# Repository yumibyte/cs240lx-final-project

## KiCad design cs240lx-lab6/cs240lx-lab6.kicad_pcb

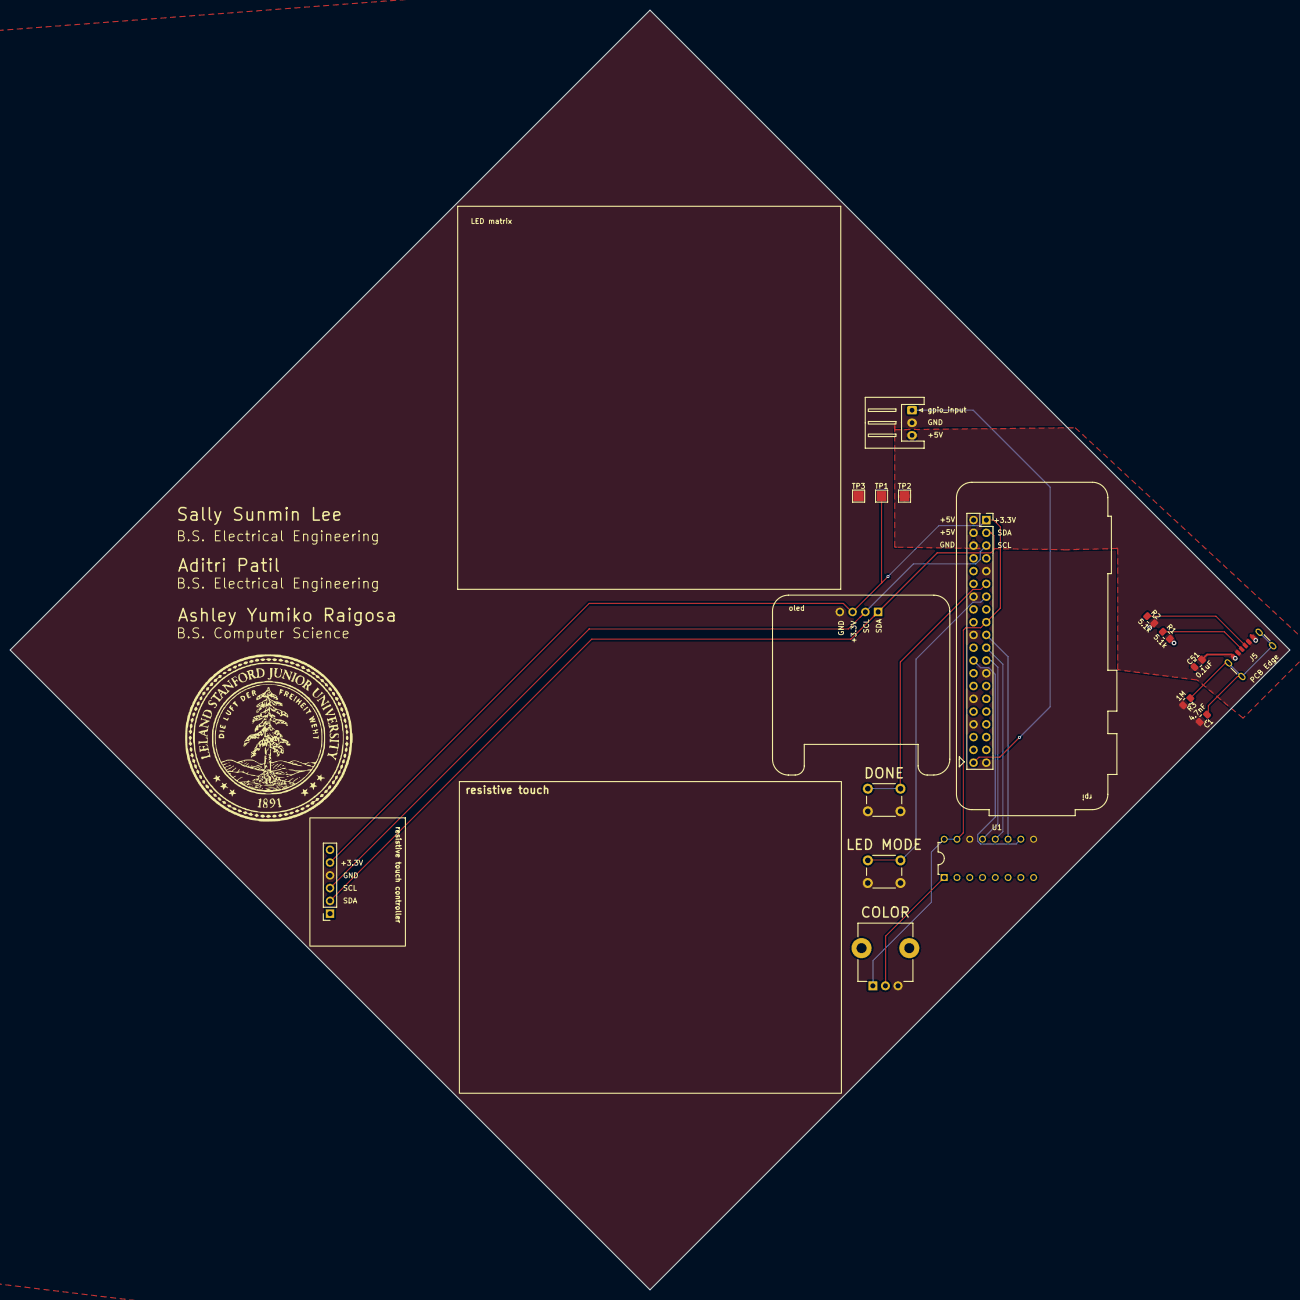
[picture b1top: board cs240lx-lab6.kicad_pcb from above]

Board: 2 copper layers, 254.6 x 254.6 mm, 17 parts (0 on the bottom side), 16 nets.

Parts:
C1: 4.7nF; C_0805_2012Metric_Pad1.18x1.45mm_HandSolder
C51: 0.1uF; C_0805_2012Metric_Pad1.18x1.45mm_HandSolder
COLOR: Potentiometer; Potentiometer_TT_P0915N
DONE: SW_Push; SW_PUSH_6mm
J1: Raspberry_Pi_2_3; PinSocket_2x20_P2.54mm_Vertical_rpi
J2: Conn_01x04_Socket; Adafruit_SSD1306_No_Mounting_Holes_oled
J3: Conn_01x03_Socket; JST_XH_S3B-XH-A_1x03_P2.50mm_Horizontal_led
J4: Conn_01x06_Socket; PinSocket_1x06_P2.54mm_Vertical_resistive_touch
J5: USB_C_Receptacle_PowerOnly_6P; USB_C_Receptacle_GCT_USB4125-xx-x_6P_TopMnt_Horizontal
LED MODE: SW_Push; SW_PUSH_6mm
R1, R2: 5.1k; R_0805_2012Metric_Pad1.20x1.40mm_HandSolder
R3: 1M; R_0805_2012Metric_Pad1.20x1.40mm_HandSolder
TP1: +3.3V; TestPoint_Pad_2.0x2.0mm
TP2: +5V; TestPoint_Pad_2.0x2.0mm
TP3: GND; TestPoint_Pad_2.0x2.0mm
U1: MCP3008; adc

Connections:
+3.3V: COLOR.1, J1.1 (3V3), J1.17 (3V3), J2.3, J4.5, TP1.1 (1_1), U1.15 (Vref), U1.16 (Vdd)
+5V: C51.1, J1.2 (5V), J1.4 (5V), J3.3, J5.A9 (VBUS), J5.B9 (VBUS), TP2.1 (1_1)
/CS: J1.24 (~CE0/GPIO8), U1.10 (~CS/SHDN)
/MISO: J1.21 (MISO0/GPIO9), U1.12 (Dout)
/MOSI: J1.19 (MOSI0/GPIO10), U1.11 (Din)
/SCL: J1.5 (SCL/GPIO3), J2.2, J4.3
/SCLK: J1.23 (SCLK0/GPIO11), U1.13 (CLK)
/SDA: J1.3 (SDA/GPIO2), J2.1, J4.2
/gpio_17: DONE.1, J1.11 (GPIO17)
/gpio_27: J1.13 (GPIO27), LED MODE.1
/gpio_input: J1.40 (GPIO21/SCLK1), J3.1
GND: C1.2, C51.2, COLOR.3, DONE.2, J1.6 (GND), J1.9 (GND), J1.14 (GND), J1.20 (GND), J1.25 (GND), J1.30 (GND), J1.34 (GND), J1.39 (GND), J2.4, J3.2, J4.4, J5.A12 (GND), J5.B12 (GND), LED MODE.2, R1.2, R2.2, R3.2, TP3.1 (1_1), U1.9 (DGND), U1.14 (AGND)
unnamed: J5.A5 (CC1), R1.1
unnamed: J5.B5 (CC2), R2.1
unnamed: C1.1, J5.SH (SHIELD), R3.1
unnamed: COLOR.2, U1.1 (CH0)

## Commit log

2026-05-28 files
2026-06-05 kicad files
2026-06-06 baseline
2026-06-06 remove
2026-06-07 finished bluetooth lab
2026-06-07 sallys code
2026-06-07 move for my sanity
2026-06-09 bmp examples
2026-06-09 basic leds
2026-06-09 leds
2026-06-09 oled, compression
2026-06-09 Add working BLE zip transfer + iOS yearbook app
2026-06-09 basic bluetooth integration
2026-06-09 Improve signature capture, BLE fetch, and yearbook layout.
    Fix BMP vs OLED orientation, connect nearby touch samples, speed up save countdown, correct WS2812 include paths, and tighten yearbook collage spacing.
2026-06-09 Add interactive yearbook editor with collage export.
    Tap signatures to select, move, resize, and rotate them; pick ink colors; remove and restore placements; save the composed collage to Photos.
2026-06-09 Fix yearbook ink rendering, performance, and add app icon.
    Crop signature whitespace, tint only stroke pixels with pastel inks, cache rendered images for smooth editing, fix iOS 16 build issues, and wire 1024×1024 AppIcon asset catalog.
2026-06-10 pot, gpios
